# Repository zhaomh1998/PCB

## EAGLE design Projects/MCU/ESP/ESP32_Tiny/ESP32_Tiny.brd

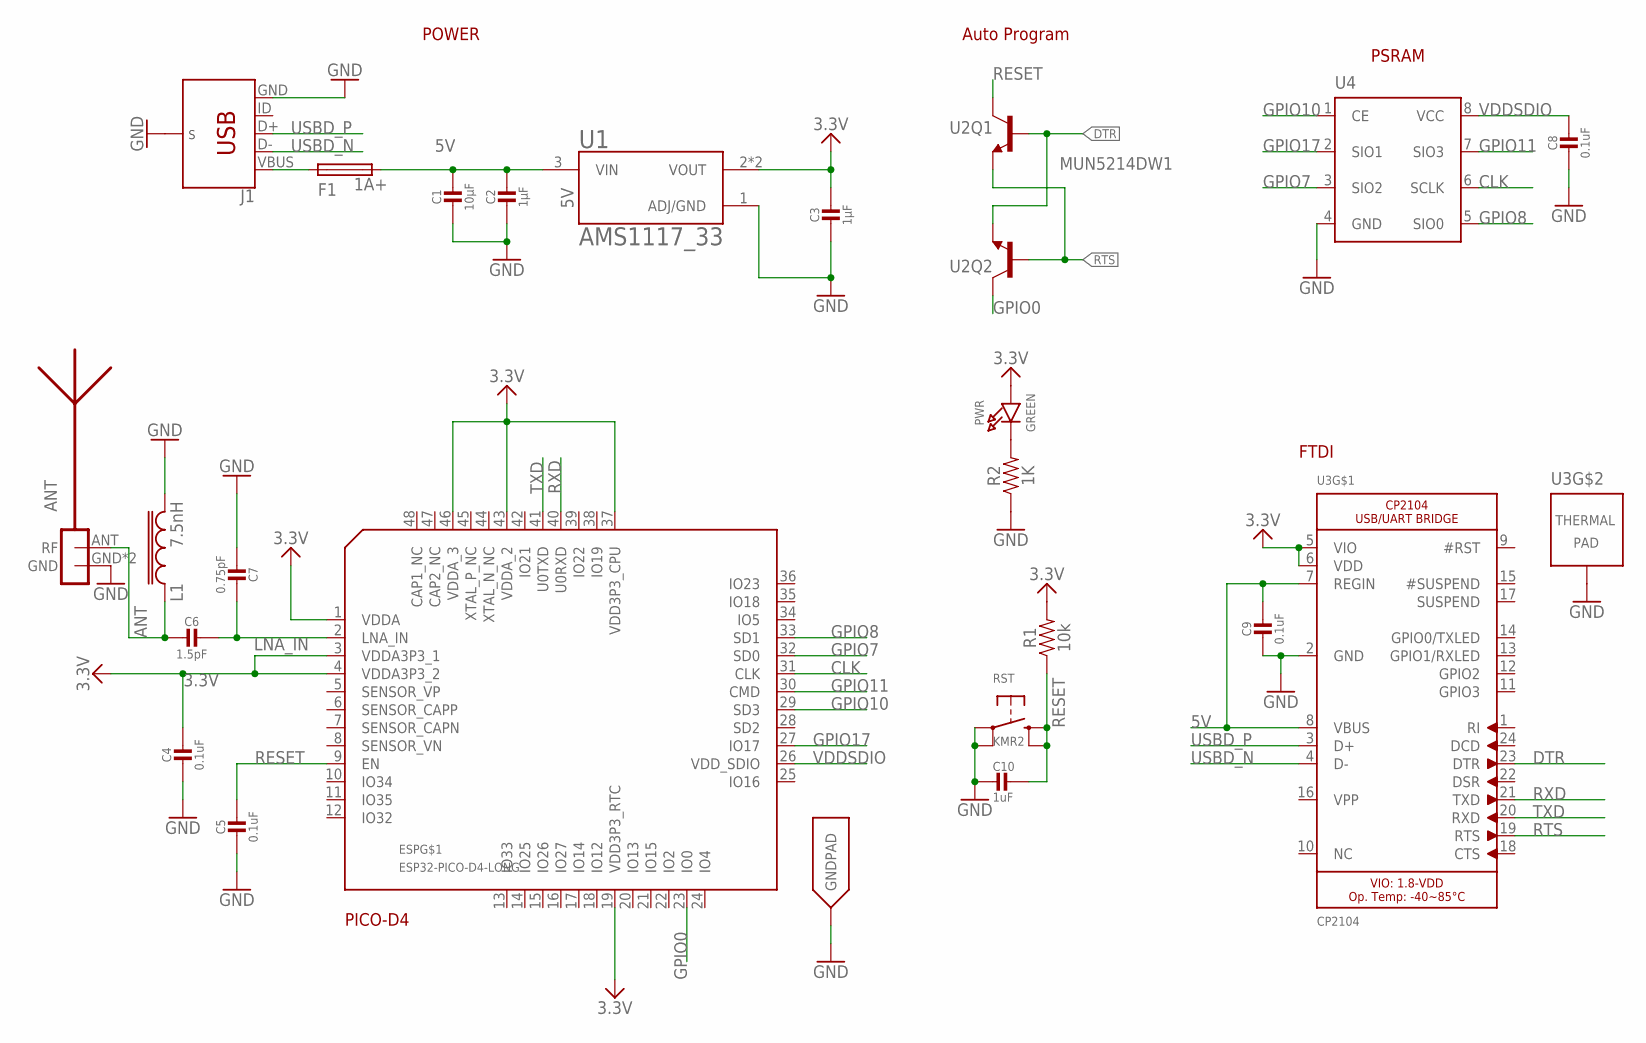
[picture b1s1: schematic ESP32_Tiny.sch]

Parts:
ANT: AN043_2.45GREV1_RIGHT; AN043_RIGHT
C1: 10µF; 0805
C2, C3: 1µF; 0603
C4, C5, C8, C9: 0.1uF; 0603
C6: 1.5pF; 0603
C7: 0.75pF; 0603
C10: 1uF; 0603
ESP: ESP32-PICO-D4-LONG; PICO-D4-QFN48-LONG
F1: 1A+; 1206
J1: USB-MICRO-B-SOCKET-2
L1: 7.5nH; 0603
PWR: GREEN; CHIPLED_0603
R1: 10k; 0603
R2: 1K; 0603
RST: KMR2; BTN_KMR2_4.6X2.8
U1: AMS1117_33; SOT89
U2: MUN5214DW1; DUAL_NPN_SC70-6
U3: CP2104; QFN24_4MM_SMSC_LONG
U4: LY68L6400SLIT; SOP8

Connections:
3.3V: C3.1, C4.1, ESP.1 (VDDA), ESP.3 (VDDA3P3_1), ESP.4 (VDDA3P3_2), ESP.19 (VDD3P3_RTC), ESP.37 (VDD3P3_CPU), ESP.43 (VDDA_2), ESP.46 (VDDA_3), PWR.A, R1.2, U1.2 (VOUT), U1.2@1 (VOUT), U3.5 (VIO), U3.6 (VDD)
5V: C1.1, C2.1, C9.1, F1.2, U1.3 (VIN), U3.7 (REGIN), U3.8 (VBUS)
ANT: ANT.ANT (RF), C6.2, L1.1
CLK: ESP.31 (CLK), U4.6 (SCLK)
DTR: U2.1 (E), U2.5 (B), U3.23 (DTR)
GND: ANT.GND, ANT.GND-PAD1 (GND), C1.2, C2.2, C3.2, C4.2, C5.2, C7.2, C8.2, C9.2, C10.2, ESP.EXP (GNDPAD), J1.GND, J1.S1 (SHIELD), J1.S2 (SHIELD), J1.S3 (SHIELD), J1.S4 (SHIELD), J1.S5 (SHIELD), L1.2, R2.1, RST.A, RST.A' (P1), U1.1 (ADJ/GND), U3.2 (GND), U3.THERM (TP), U4.4 (GND)
GPIO0: ESP.23 (IO0), U2.6 (C)
GPIO7: ESP.32 (SD0), U4.3 (SIO2)
GPIO8: ESP.33 (SD1), U4.5 (SIO0)
GPIO10: ESP.29 (SD3), U4.1 (CE)
GPIO11: ESP.30 (CMD), U4.7 (SIO3)
GPIO17: ESP.27 (IO17), U4.2 (SIO1)
LNA_IN: C6.1, C7.1, ESP.2 (LNA_IN)
unnamed: F1.1, J1.VBUS
unnamed: PWR.C, R2.2
RESET: C5.1, C10.1, ESP.9 (EN), R1.1, RST.B (S), RST.B' (S1), U2.3 (C)
RTS: U2.2 (B), U2.4 (E), U3.19 (RTS)
RXD: ESP.40 (U0RXD), U3.21 (TXD)
TXD: ESP.41 (U0TXD), U3.20 (RXD)
USBD_N: J1.D-, U3.4 (D-)
USBD_P: J1.D+, U3.3 (D+)
VDDSDIO: C8.1, ESP.26 (VDD_SDIO), U4.8 (VCC)

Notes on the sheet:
POWER
FTDI
PICO-D4
PSRAM
Auto Program

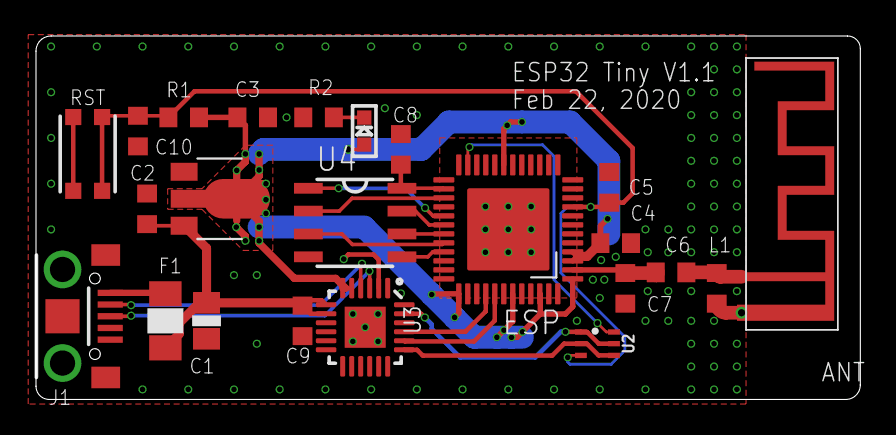
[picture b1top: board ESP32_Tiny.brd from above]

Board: 2 copper layers, 45.8 x 20.2 mm, 23 parts (0 on the bottom side), 22 nets.

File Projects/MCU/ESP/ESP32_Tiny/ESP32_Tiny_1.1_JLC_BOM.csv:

Comment,Designator,Footprint,LCSC Part #
10uF (106) ±10% 25V X5R,C1,805,C15850
1uF 0603,"C2,C3",603,C15849
0.1uF 0603,"C4,C5,C8,C9",603, C14663
1.5pF 0603,C6,603,C1639
0.75pF 0603,C7,603,C170124
ESP32-Pico-D4,ESP,,C193707
7.5nH 0603,L1,603,C395093
LED 0603,PWR,603,C72043
1K 0603,R1,603,C21190
10K 0603,R2,603,C25804
KMR211GLFS SWITCH TACTILE SPST-NO 0.05A 32V,RST,,
AMS1117,U1,SOT89,C108493
MUN5214DW1T1G TRANS 2NPN PREBIAS 0.25W SOT363,U2,SOT363,C94403
CP2104 IC SGL USB-TO-UART BRIDGE 24QFN,U3,24QFN,C47742
LY68L6400SLT Volatile 64Mb (8M x 8) SPI/ QPI 2.7V ~ 3.6V SOP-8_150mil RAM RoHS,U4,SOP8,C261881

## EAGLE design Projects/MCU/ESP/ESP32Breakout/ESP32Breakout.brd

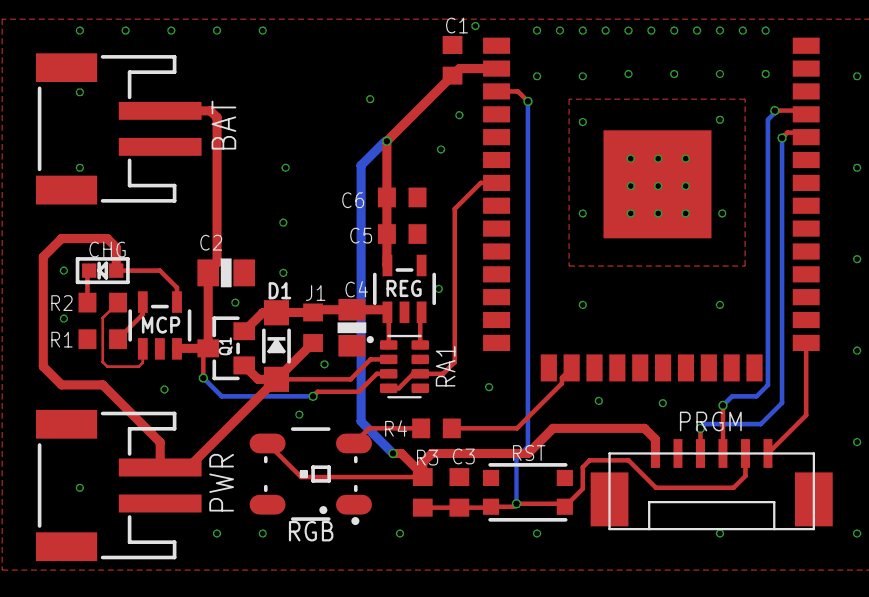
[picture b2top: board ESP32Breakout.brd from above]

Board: 2 copper layers, 23 parts (0 on the bottom side), 16 nets.

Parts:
BAT: JSTPH; JST_PH_2.0_2P
C1: 0.1uF; 0603
C2, C4: 10µF; 0805
C3, C5: 1uF; 0603
C6: 10µF; 0603
CHG: CHIPLED_0603
D1: MBR120; SOD-123
J1: 0603
MCP: MCP73831; MICROBUILDER_SOT23-5
PRGM: JST_1.25_6P; JST1.25_6P
PWR: JST_PH_2.0_2P
Q1: DMG3415U; SOT23-WIDE
R1: 4.7k; 0603
R2: 1k; 0603
R3: 10k; 0603
R4: 0603
RA1: RESCAF80P320X160X60-8N
REG: AP2112-3.3; MICROBUILDER_SOT23-5
RGB: LED_WS2812; LED-TRICOLOR-5050-IC
RST: KMR2; BTN_KMR2_4.6X2.8
X2: ESP32_WROOM32; WROOM32

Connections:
3.3V: C1.1, C5.1, C6.1, PRGM.6, R3.2, REG.5, RGB.VDD, X2.2
A13_I35: RA1.4, RA1.6, X2.7
EN: RA1.8, REG.3
GND: BAT.1, C1.2, C2.2, C3.2, C4.2, C5.2, C6.2, MCP.2, PRGM.5, PWR.1, R1.2, RA1.5, RA1.7, REG.2, RGB.VSS, RST.A, RST.A', X2.1, X2.15, X2.38, X2.P$1
GPIO0: PRGM.1, X2.25
IO13_A12: R4.2, X2.16
unnamed: CHG.C, R2.1
unnamed: R4.1, RGB.DIN
unnamed: MCP.1, R2.2
unnamed: MCP.5, R1.1
unnamed: C4.1, D1.C, J1.2, Q1.2, RA1.1, REG.1
RESET: C3.1, PRGM.2, R3.1, RST.B, RST.B', X2.3
RXD0: PRGM.4, X2.34
TXD0: PRGM.3, X2.35
VBAT: BAT.2, C2.1, MCP.3, Q1.3, RA1.3
VBUS: CHG.A, D1.A, J1.1, MCP.4, PWR.2, Q1.1, RA1.2

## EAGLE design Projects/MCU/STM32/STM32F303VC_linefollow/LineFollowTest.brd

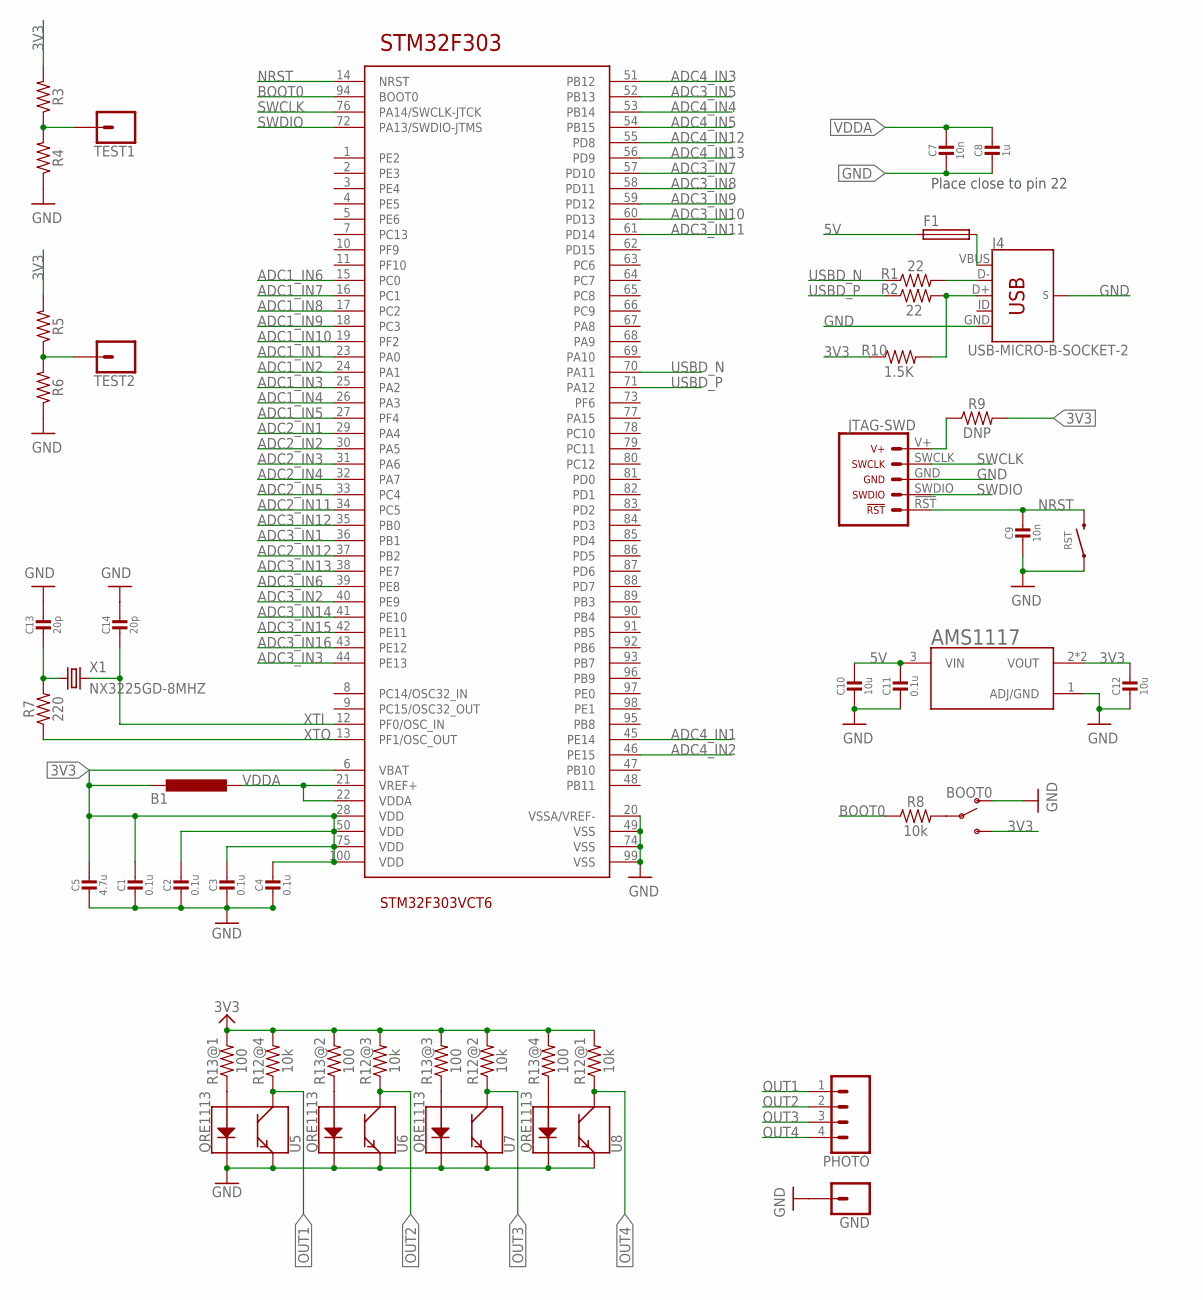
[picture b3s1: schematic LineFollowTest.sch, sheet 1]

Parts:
AMS1117: 3.3V; SOT89
B1: BEAD-0603; 0603
BOOT0: SWITCH_SPDT_SLIDE; SWITCH_SPDT_PTH_11.6X4.0MM
C1, C2, C3, C4, C11: 0.1u; CAP_0603
C5: 4.7u; CAP_0603
C7, C9: 10n; CAP_0603
C8: 1u; CAP_0603
C10, C12: 10u; CAP_0603
C13, C14: 20p; CAP_0603
F1: FUSE-1206; 1206
GND: THD_01; 1X01
J4: USB-MICRO-B-SOCKET-2
PHOTO: CONN_04PTH; 1X04
R1, R2: 22; 0603
R3, R4, R5, R6: 0603
R7: 220; 0603
R8: 10k; 0603
R9: DNP; 0603
R10: 1.5K; 0603
R12: 10k; RESCAF80P320X160X60-8N
R13: 100; RESCAF80P320X160X60-8N
RST: PUSHBUTTON; TACTILE_SWITCH_SMD_6.0X3.5MM
STM32F303: STM32F303VCT6; LQFP-100
TEST1, TEST2: THD_01; 1X01
U5, U6, U7, U8: QRE1113; QRE1113-W
U$3: JTAG-SWD; JTAG_SWD
X1: NX3225GD-8MHZ; XTAL-SMD-3225

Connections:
3V3: AMS1117.2 (VOUT), AMS1117.2@1 (VOUT), B1.1, BOOT0.3 (S), C1.1, C2.1, C3.1, C4.1, C5.1, C12.1, R3.2, R5.2, R9.2, R10.1, R12.5 (2), R12.6 (2), R12.7 (2), R12.8 (2), R13.5 (2), R13.6 (2), R13.7 (2), R13.8 (2), STM32F303.6 (VBAT), STM32F303.28 (VDD), STM32F303.50 (VDD), STM32F303.75 (VDD), STM32F303.100 (VDD)
5V: AMS1117.3 (VIN), C10.1, C11.1, F1.1
ADC1_IN1: STM32F303.23 (PA0); also elsewhere on the board
ADC1_IN2: STM32F303.24 (PA1); also elsewhere on the board
ADC1_IN3: STM32F303.25 (PA2); also elsewhere on the board
ADC1_IN4: STM32F303.26 (PA3); also elsewhere on the board
ADC1_IN5: STM32F303.27 (PF4); also elsewhere on the board
ADC1_IN6: STM32F303.15 (PC0); also elsewhere on the board
ADC1_IN7: STM32F303.16 (PC1); also elsewhere on the board
ADC1_IN8: STM32F303.17 (PC2); also elsewhere on the board
ADC1_IN9: STM32F303.18 (PC3); also elsewhere on the board
ADC1_IN10: STM32F303.19 (PF2); also elsewhere on the board
ADC2_IN1: STM32F303.29 (PA4); also elsewhere on the board
ADC2_IN2: STM32F303.30 (PA5); also elsewhere on the board
ADC2_IN3: STM32F303.31 (PA6); also elsewhere on the board
ADC2_IN4: STM32F303.32 (PA7); also elsewhere on the board
ADC2_IN5: STM32F303.33 (PC4); also elsewhere on the board
ADC2_IN11: STM32F303.34 (PC5); also elsewhere on the board
ADC2_IN12: STM32F303.37 (PB2); also elsewhere on the board
ADC3_IN1: STM32F303.36 (PB1); also elsewhere on the board
ADC3_IN2: STM32F303.40 (PE9); also elsewhere on the board
ADC3_IN3: STM32F303.44 (PE13); also elsewhere on the board
ADC3_IN5: STM32F303.52 (PB13); also elsewhere on the board
ADC3_IN6: STM32F303.39 (PE8); also elsewhere on the board
ADC3_IN7: STM32F303.57 (PD10); also elsewhere on the board
ADC3_IN8: STM32F303.58 (PD11); also elsewhere on the board
ADC3_IN9: STM32F303.59 (PD12); also elsewhere on the board
ADC3_IN10: STM32F303.60 (PD13); also elsewhere on the board
ADC3_IN11: STM32F303.61 (PD14); also elsewhere on the board
ADC3_IN12: STM32F303.35 (PB0); also elsewhere on the board
ADC3_IN13: STM32F303.38 (PE7); also elsewhere on the board
ADC3_IN14: STM32F303.41 (PE10); also elsewhere on the board
ADC3_IN15: STM32F303.42 (PE11); also elsewhere on the board
ADC3_IN16: STM32F303.43 (PE12); also elsewhere on the board
ADC4_IN1: STM32F303.45 (PE14); also elsewhere on the board
ADC4_IN2: STM32F303.46 (PE15); also elsewhere on the board
ADC4_IN3: STM32F303.51 (PB12); also elsewhere on the board
ADC4_IN4: STM32F303.53 (PB14); also elsewhere on the board
ADC4_IN5: STM32F303.54 (PB15); also elsewhere on the board
ADC4_IN12: STM32F303.55 (PD8); also elsewhere on the board
ADC4_IN13: STM32F303.56 (PD9); also elsewhere on the board
BOOT0: R8.1, STM32F303.94 (BOOT0)
GND: AMS1117.1 (ADJ/GND), BOOT0.1 (O), C1.2, C2.2, C3.2, C4.2, C5.2, C7.2, C8.2, C9.2, C10.2, C11.2, C12.2, C13.1, C14.1, GND.1, J4.GND, J4.S1 (SHIELD), J4.S2 (SHIELD), J4.S3 (SHIELD), J4.S4 (SHIELD), J4.S5 (SHIELD), R4.1, R6.1, RST.1, STM32F303.20 (VSSA/VREF-), STM32F303.49 (VSS), STM32F303.74 (VSS), STM32F303.99 (VSS), U5.2 (K), U5.4 (E), U6.2 (K), U6.4 (E), U7.2 (K), U7.4 (E), U8.2 (K), U8.4 (E), U$3.GND
unnamed: R5.1, R6.2, TEST2.1
unnamed: C13.2, R7.2, X1.1
unnamed: BOOT0.2, R8.2
unnamed: R9.1, U$3.V+
unnamed: R3.1, R4.2, TEST1.1
unnamed: F1.2, J4.VBUS
unnamed: J4.D-, R1.2
unnamed: J4.D+, R2.2, R10.2
unnamed: R13.1, U5.1 (A)
unnamed: R13.2 (1), U6.1 (A)
unnamed: R13.3 (1), U7.1 (A)
unnamed: R13.4 (1), U8.1 (A)
NRST: C9.1, RST.2, STM32F303.14 (NRST), U$3.!RST
OUT1: PHOTO.1, R12.4 (1), U5.3 (C)
OUT2: PHOTO.2, R12.3 (1), U6.3 (C)
OUT3: PHOTO.3, R12.2 (1), U7.3 (C)
OUT4: PHOTO.4, R12.1, U8.3 (C)
SWCLK: STM32F303.76 (PA14/SWCLK-JTCK), U$3.SWCLK
SWDIO: STM32F303.72 (PA13/SWDIO-JTMS), U$3.SWDIO
USBD_N: R1.1, STM32F303.70 (PA11)
USBD_P: R2.1, STM32F303.71 (PA12)
VDDA: B1.2, C7.1, C8.1, STM32F303.21 (VREF+), STM32F303.22 (VDDA)
XTI: C14.2, STM32F303.12 (PF0/OSC_IN), X1.2
XTO: R7.1, STM32F303.13 (PF1/OSC_OUT)

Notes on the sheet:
Place close to pin 22

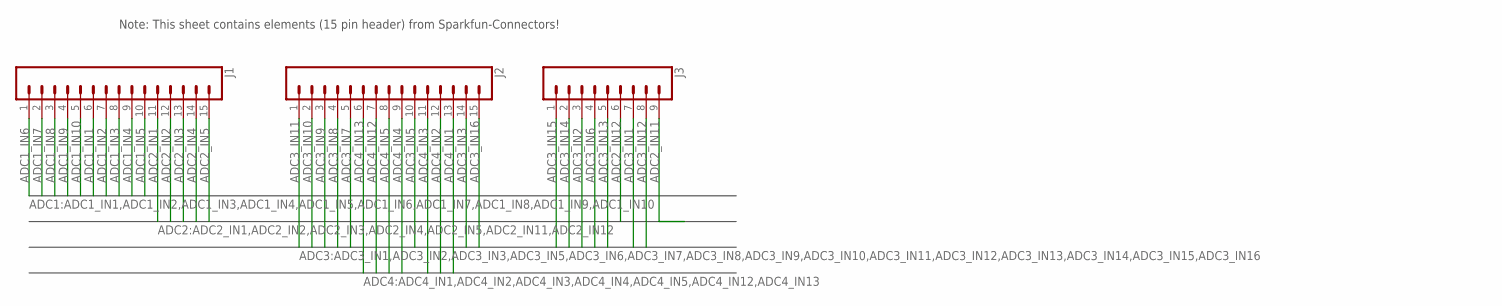
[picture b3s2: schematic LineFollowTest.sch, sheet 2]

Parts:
J1, J2: CONN_15; 1X15
J3: CONN_09; 1X09

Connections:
ADC1_IN1: J1.6; also elsewhere on the board
ADC1_IN2: J1.7; also elsewhere on the board
ADC1_IN3: J1.8; also elsewhere on the board
ADC1_IN4: J1.9; also elsewhere on the board
ADC1_IN5: J1.10; also elsewhere on the board
ADC1_IN6: J1.1; also elsewhere on the board
ADC1_IN7: J1.2; also elsewhere on the board
ADC1_IN8: J1.3; also elsewhere on the board
ADC1_IN9: J1.4; also elsewhere on the board
ADC1_IN10: J1.5; also elsewhere on the board
ADC2_IN1: J1.11; also elsewhere on the board
ADC2_IN2: J1.12; also elsewhere on the board
ADC2_IN3: J1.13; also elsewhere on the board
ADC2_IN4: J1.14; also elsewhere on the board
ADC2_IN5: J1.15; also elsewhere on the board
ADC2_IN11: J3.9; also elsewhere on the board
ADC2_IN12: J3.6; also elsewhere on the board
ADC3_IN1: J3.7; also elsewhere on the board
ADC3_IN2: J3.3; also elsewhere on the board
ADC3_IN3: J2.14; also elsewhere on the board
ADC3_IN5: J2.10; also elsewhere on the board
ADC3_IN6: J3.4; also elsewhere on the board
ADC3_IN7: J2.5; also elsewhere on the board
ADC3_IN8: J2.4; also elsewhere on the board
ADC3_IN9: J2.3; also elsewhere on the board
ADC3_IN10: J2.2; also elsewhere on the board
ADC3_IN11: J2.1; also elsewhere on the board
ADC3_IN12: J3.8; also elsewhere on the board
ADC3_IN13: J3.5; also elsewhere on the board
ADC3_IN14: J3.2; also elsewhere on the board
ADC3_IN15: J3.1; also elsewhere on the board
ADC3_IN16: J2.15; also elsewhere on the board
ADC4_IN1: J2.13; also elsewhere on the board
ADC4_IN2: J2.12; also elsewhere on the board
ADC4_IN3: J2.11; also elsewhere on the board
ADC4_IN4: J2.9; also elsewhere on the board
ADC4_IN5: J2.8; also elsewhere on the board
ADC4_IN12: J2.7; also elsewhere on the board
ADC4_IN13: J2.6; also elsewhere on the board

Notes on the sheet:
Note: This sheet contains elements (15 pin header) from Sparkfun-Connectors!

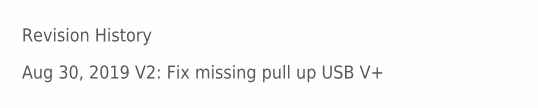
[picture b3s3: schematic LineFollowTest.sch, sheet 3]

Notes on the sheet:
Revision History
Aug 30, 2019 V2: Fix missing pull up USB V+

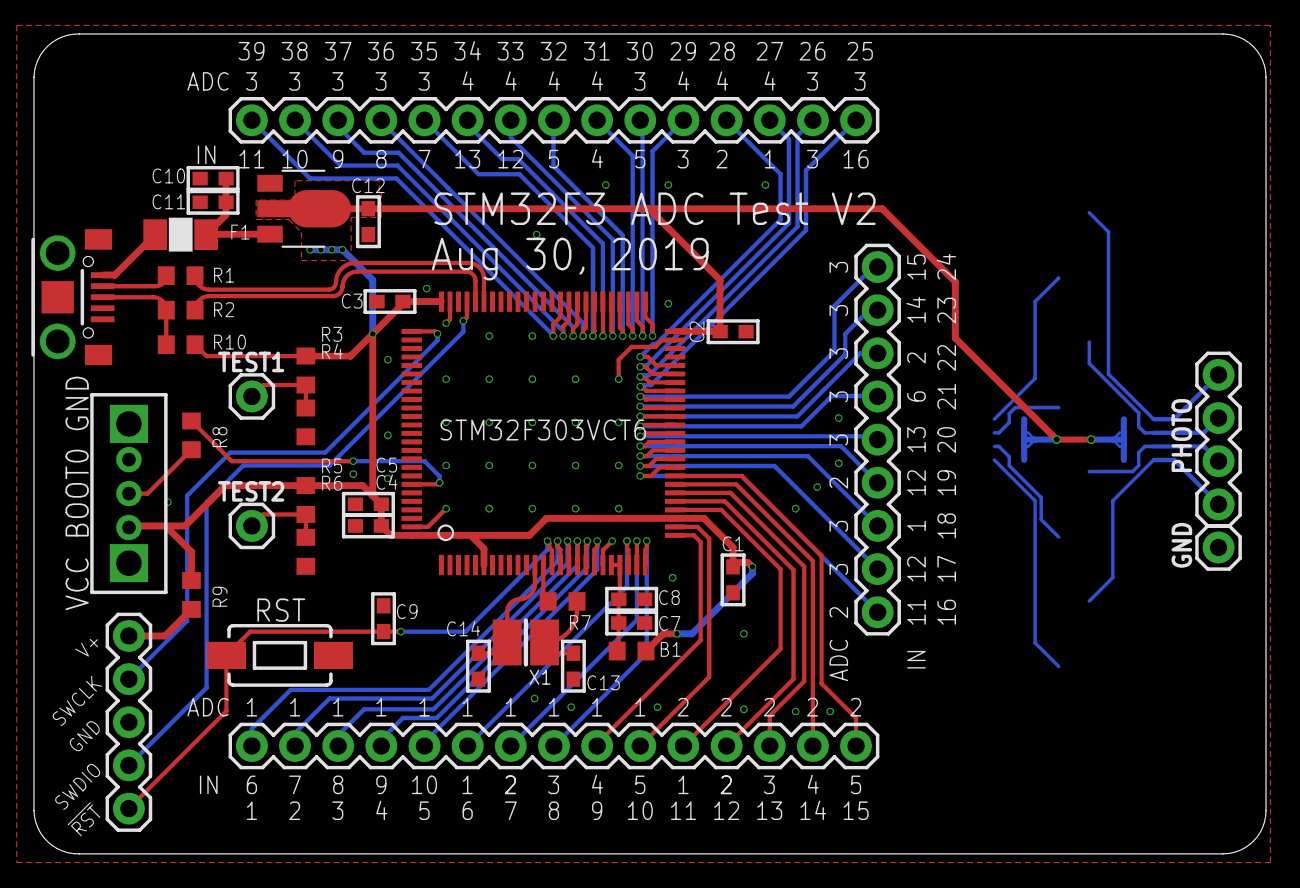
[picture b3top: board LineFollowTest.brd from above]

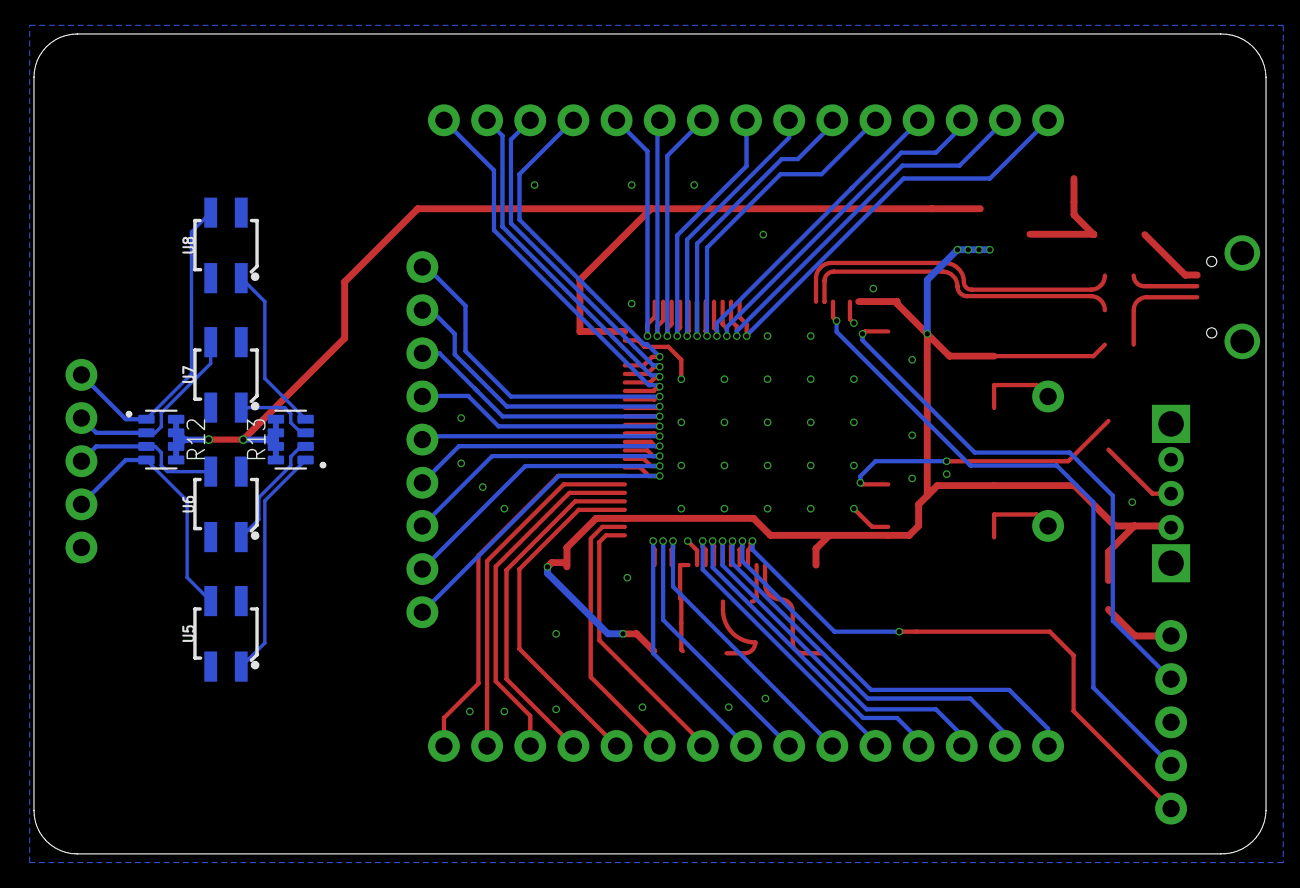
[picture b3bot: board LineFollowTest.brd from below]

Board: 2 copper layers, 72.5 x 48.3 mm, 45 parts (6 on the bottom side), 67 nets.

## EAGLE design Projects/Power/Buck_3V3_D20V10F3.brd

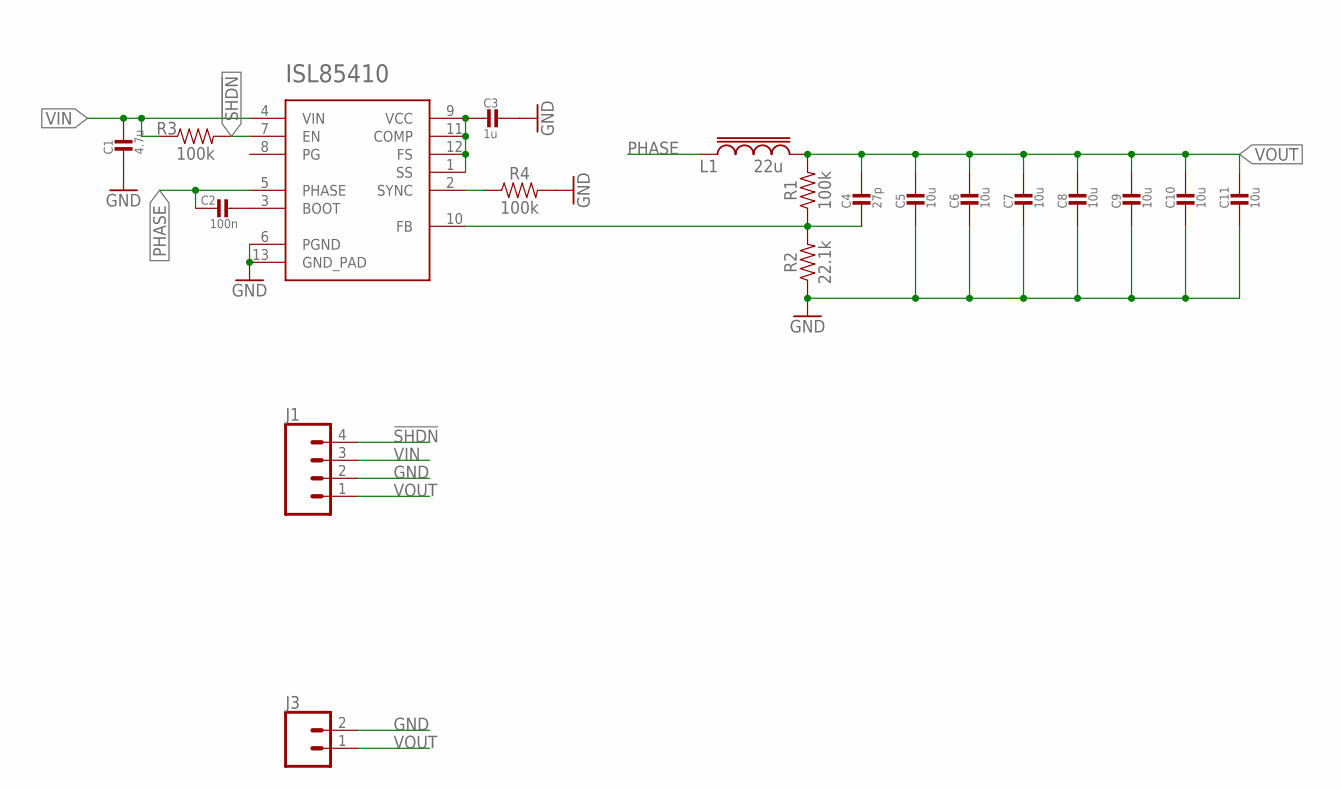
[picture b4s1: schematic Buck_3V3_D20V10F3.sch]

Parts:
C1: 4.7u; 0603
C2: 100n; 0603
C3: 1u; 0603
C4: 27p; 0603
C5, C6, C7, C8, C9, C10, C11: 10u; 0805
ISL85410: BUCK_ISL85410; DFN-12_DE-L
J1: CONN_041X04_NO_SILK; 1X04_NO_SILK
J3: CONN_021X02_NO_SILK; 1X02_NO_SILK
L1: 22u; CD54
R1, R3, R4: 100k; 0603
R2: 22.1k; 0603

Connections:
!SHDN: ISL85410.7 (EN), J1.4, R3.2
BOOT: C2.1, ISL85410.3 (BOOT)
FB: C4.2, ISL85410.10 (FB), R1.1, R2.2
GND: C1.2, C3.1, C5.2, C6.2, C7.2, C8.2, C9.2, C10.2, C11.2, ISL85410.6 (PGND), ISL85410.13 (GND_PAD), J1.2, J3.2, R2.1, R4.2
PHASE: C2.2, ISL85410.5 (PHASE), L1.P$1
SYNC: ISL85410.2 (SYNC), R4.1
VCC: C3.2, ISL85410.1 (SS), ISL85410.9 (VCC), ISL85410.11 (COMP), ISL85410.12 (FS)
VIN: C1.1, ISL85410.4 (VIN), J1.3, R3.1
VOUT: C4.1, C5.1, C6.1, C7.1, C8.1, C9.1, C10.1, C11.1, J1.1, J3.1, L1.P$2, R1.2

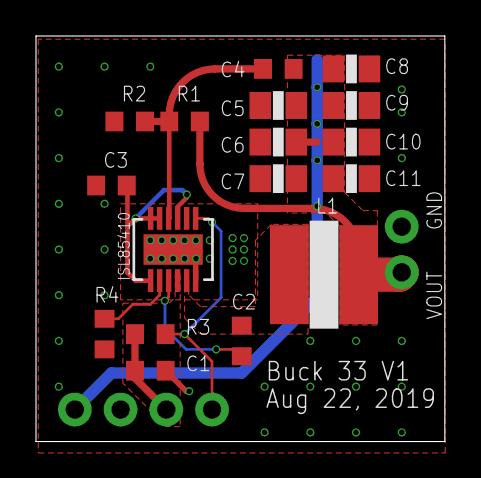
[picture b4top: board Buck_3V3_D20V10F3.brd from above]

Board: 2 copper layers, 22.7 x 22.5 mm, 19 parts (0 on the bottom side), 9 nets.

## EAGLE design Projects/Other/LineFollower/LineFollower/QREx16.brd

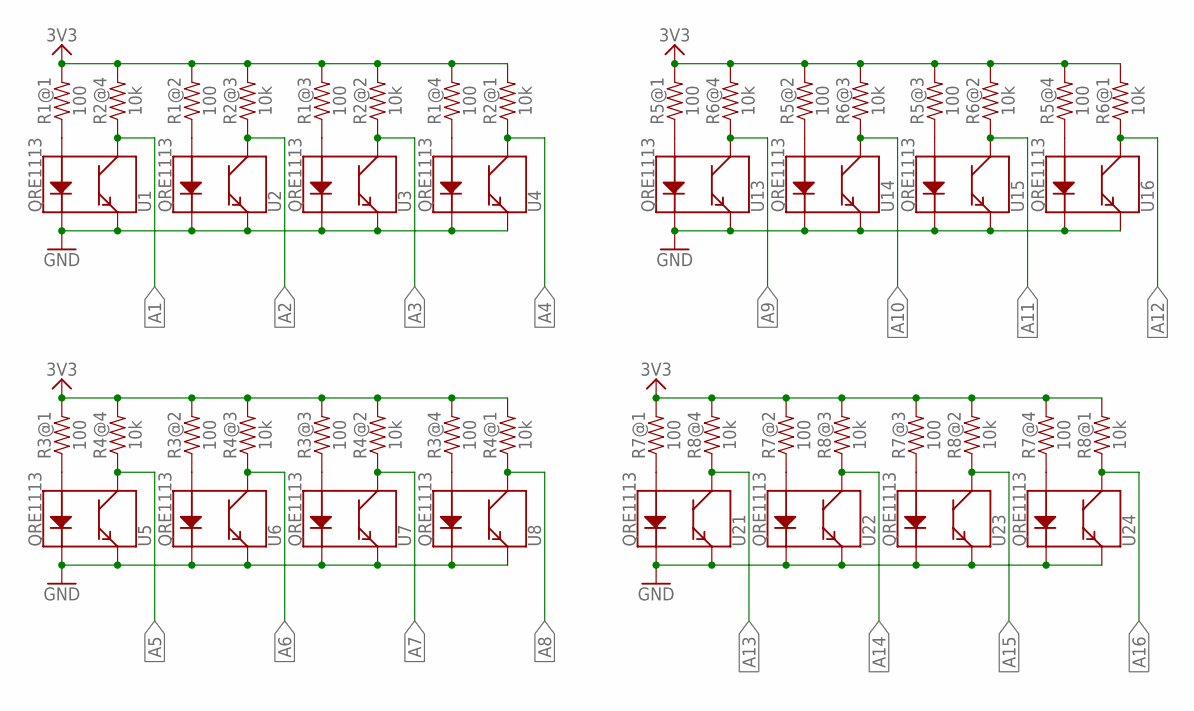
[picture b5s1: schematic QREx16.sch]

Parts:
R1, R3, R5, R7: 100; RESCAF80P320X160X60-8N
R2, R4, R6, R8: 10k; RESCAF80P320X160X60-8N
U1, U2, U3, U4, U5, U6, U7, U8, U13, U14, U15, U16, U21, U22, U23, U24: QRE1113; QRE1113-W

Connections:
3.3V: R1.5 (2), R1.6 (2), R1.7 (2), R1.8 (2), R2.5 (2), R2.6 (2), R2.7 (2), R2.8 (2), R3.5 (2), R3.6 (2), R3.7 (2), R3.8 (2), R4.5 (2), R4.6 (2), R4.7 (2), R4.8 (2), R5.5 (2), R5.6 (2), R5.7 (2), R5.8 (2), R6.5 (2), R6.6 (2), R6.7 (2), R6.8 (2), R7.5 (2), R7.6 (2), R7.7 (2), R7.8 (2), R8.5 (2), R8.6 (2), R8.7 (2), R8.8 (2)
A1: R2.4 (1), U1.3 (C)
A2: R2.3 (1), U2.3 (C)
A3: R2.2 (1), U3.3 (C)
A4: R2.1, U4.3 (C)
A5: R4.4 (1), U5.3 (C)
A6: R4.3 (1), U6.3 (C)
A7: R4.2 (1), U7.3 (C)
A8: R4.1, U8.3 (C)
A9: R6.4 (1), U13.3 (C)
A10: R6.3 (1), U14.3 (C)
A11: R6.2 (1), U15.3 (C)
A12: R6.1, U16.3 (C)
A13: R8.4 (1), U21.3 (C)
A14: R8.3 (1), U22.3 (C)
A15: R8.2 (1), U23.3 (C)
A16: R8.1, U24.3 (C)
GND: U1.2 (K), U1.4 (E), U2.2 (K), U2.4 (E), U3.2 (K), U3.4 (E), U4.2 (K), U4.4 (E), U5.2 (K), U5.4 (E), U6.2 (K), U6.4 (E), U7.2 (K), U7.4 (E), U8.2 (K), U8.4 (E), U13.2 (K), U13.4 (E), U14.2 (K), U14.4 (E), U15.2 (K), U15.4 (E), U16.2 (K), U16.4 (E), U21.2 (K), U21.4 (E), U22.2 (K), U22.4 (E), U23.2 (K), U23.4 (E), U24.2 (K), U24.4 (E)
unnamed: R1.1, U1.1 (A)
unnamed: R1.2 (1), U2.1 (A)
unnamed: R1.3 (1), U3.1 (A)
unnamed: R1.4 (1), U4.1 (A)
unnamed: R3.1, U5.1 (A)
unnamed: R3.2 (1), U6.1 (A)
unnamed: R3.3 (1), U7.1 (A)
unnamed: R3.4 (1), U8.1 (A)
unnamed: R5.1, U13.1 (A)
unnamed: R5.2 (1), U14.1 (A)
unnamed: R5.3 (1), U15.1 (A)
unnamed: R5.4 (1), U16.1 (A)
unnamed: R7.1, U21.1 (A)
unnamed: R7.2 (1), U22.1 (A)
unnamed: R7.3 (1), U23.1 (A)
unnamed: R7.4 (1), U24.1 (A)

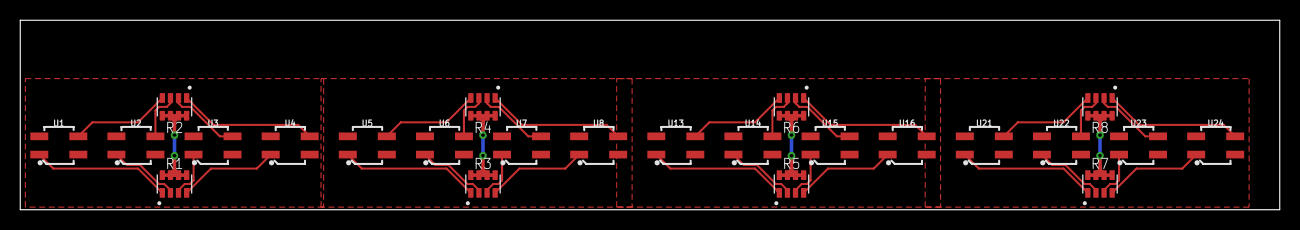
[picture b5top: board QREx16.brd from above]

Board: 2 copper layers, 124.4 x 18.7 mm, 24 parts (0 on the bottom side), 34 nets.

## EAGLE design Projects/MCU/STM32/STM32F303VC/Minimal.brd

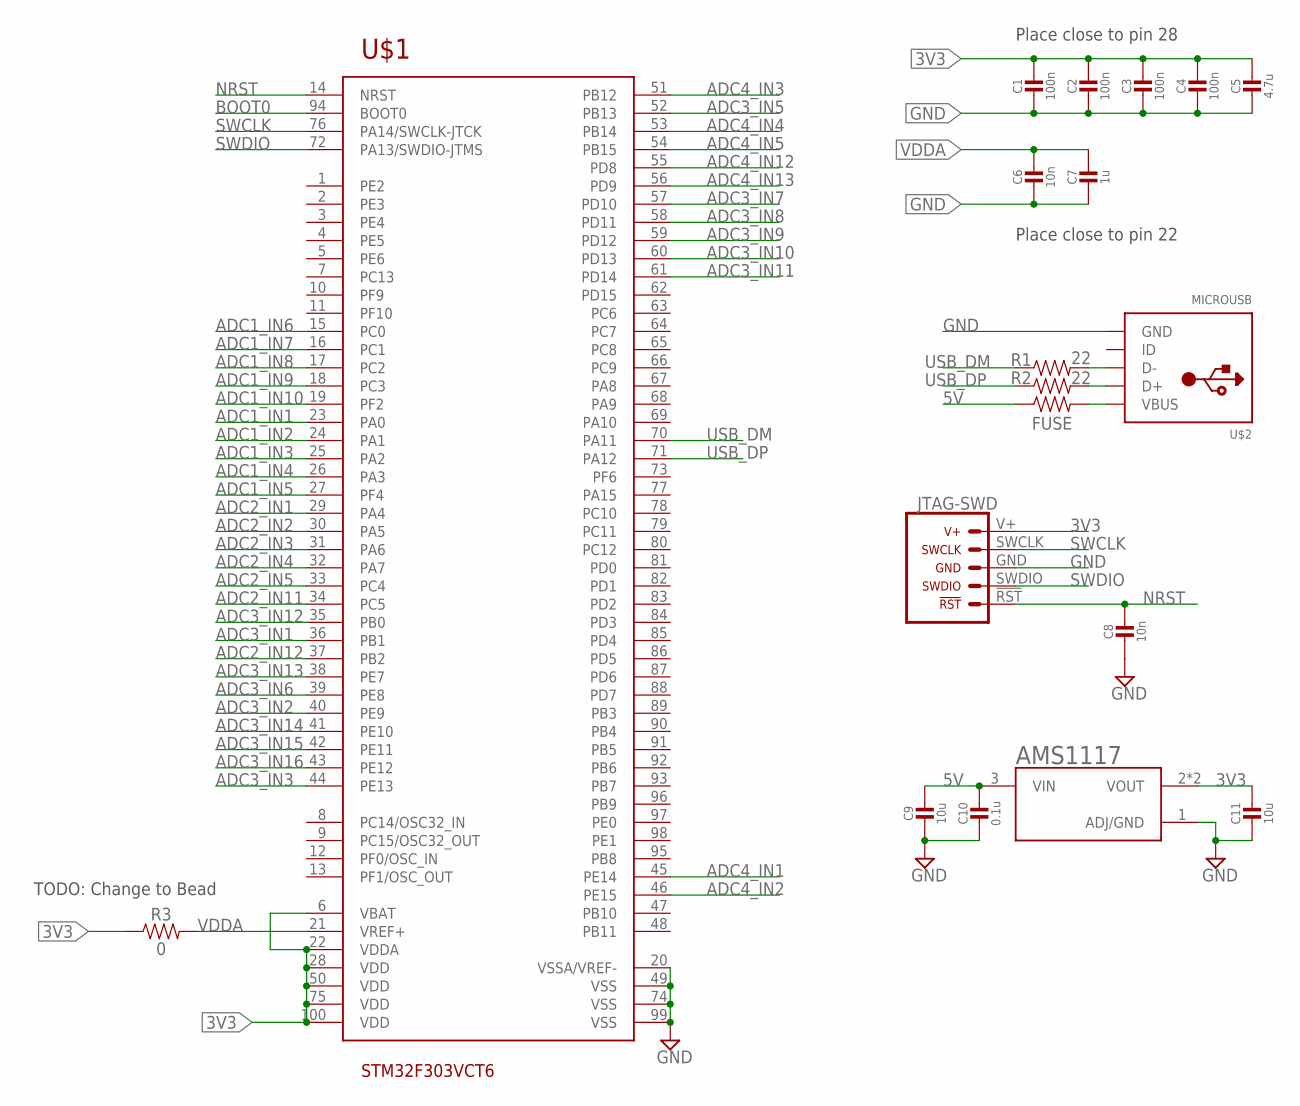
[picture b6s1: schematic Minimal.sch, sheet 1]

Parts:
AMS1117: 3.3V; SOT89
C1, C2, C3, C4: 100n; CAP_0603
C5: 4.7u; CAP_0603
C6, C8: 10n; CAP_0603
C7: 1u; CAP_0603
C9, C11: 10u; CAP_0603
C10: 0.1u; CAP_0603
FUSE: 1206
R1, R2: 22; 0603
R3: 0; 0603
U$1: STM32F303VCT6; LQFP-100
U$2: MICROUSB
U$3: JTAG-SWD; JTAG_SWD

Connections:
3V3: AMS1117.2 (VOUT), AMS1117.2@1 (VOUT), C1.1, C2.1, C3.1, C4.1, C5.1, C11.1, R3.1, U$1.6 (VBAT), U$1.22 (VDDA), U$1.28 (VDD), U$1.50 (VDD), U$1.75 (VDD), U$1.100 (VDD), U$3.V+
5V: AMS1117.3 (VIN), C9.1, C10.1, FUSE.1
ADC1_IN1: U$1.23 (PA0); also elsewhere on the board
ADC1_IN2: U$1.24 (PA1); also elsewhere on the board
ADC1_IN3: U$1.25 (PA2); also elsewhere on the board
ADC1_IN4: U$1.26 (PA3); also elsewhere on the board
ADC1_IN5: U$1.27 (PF4); also elsewhere on the board
ADC1_IN6: U$1.15 (PC0); also elsewhere on the board
ADC1_IN7: U$1.16 (PC1); also elsewhere on the board
ADC1_IN8: U$1.17 (PC2); also elsewhere on the board
ADC1_IN9: U$1.18 (PC3); also elsewhere on the board
ADC1_IN10: U$1.19 (PF2); also elsewhere on the board
ADC2_IN1: U$1.29 (PA4); also elsewhere on the board
ADC2_IN2: U$1.30 (PA5); also elsewhere on the board
ADC2_IN3: U$1.31 (PA6); also elsewhere on the board
ADC2_IN4: U$1.32 (PA7); also elsewhere on the board
ADC2_IN5: U$1.33 (PC4); also elsewhere on the board
ADC2_IN11: U$1.34 (PC5); also elsewhere on the board
ADC2_IN12: U$1.37 (PB2); also elsewhere on the board
ADC3_IN1: U$1.36 (PB1); also elsewhere on the board
ADC3_IN2: U$1.40 (PE9); also elsewhere on the board
ADC3_IN3: U$1.44 (PE13); also elsewhere on the board
ADC3_IN5: U$1.52 (PB13); also elsewhere on the board
ADC3_IN6: U$1.39 (PE8); also elsewhere on the board
ADC3_IN7: U$1.57 (PD10); also elsewhere on the board
ADC3_IN8: U$1.58 (PD11); also elsewhere on the board
ADC3_IN9: U$1.59 (PD12); also elsewhere on the board
ADC3_IN10: U$1.60 (PD13); also elsewhere on the board
ADC3_IN11: U$1.61 (PD14); also elsewhere on the board
ADC3_IN12: U$1.35 (PB0); also elsewhere on the board
ADC3_IN13: U$1.38 (PE7); also elsewhere on the board
ADC3_IN14: U$1.41 (PE10); also elsewhere on the board
ADC3_IN15: U$1.42 (PE11); also elsewhere on the board
ADC3_IN16: U$1.43 (PE12); also elsewhere on the board
ADC4_IN1: U$1.45 (PE14); also elsewhere on the board
ADC4_IN2: U$1.46 (PE15); also elsewhere on the board
ADC4_IN3: U$1.51 (PB12); also elsewhere on the board
ADC4_IN4: U$1.53 (PB14); also elsewhere on the board
ADC4_IN5: U$1.54 (PB15); also elsewhere on the board
ADC4_IN12: U$1.55 (PD8); also elsewhere on the board
ADC4_IN13: U$1.56 (PD9); also elsewhere on the board
BOOT0: U$1.94 (BOOT0)
GND: AMS1117.1 (ADJ/GND), C1.2, C2.2, C3.2, C4.2, C5.2, C6.2, C7.2, C8.2, C9.2, C10.2, C11.2, U$1.20 (VSSA/VREF-), U$1.49 (VSS), U$1.74 (VSS), U$1.99 (VSS), U$2.GND, U$2.S1 (GND), U$2.S2 (GND), U$2.S3 (GND), U$2.S4 (GND), U$2.S5 (GND), U$2.S6 (GND), U$3.GND
unnamed: FUSE.2, U$2.VBUS
unnamed: R2.2, U$2.D+
unnamed: R1.2, U$2.D-
NRST: C8.1, U$1.14 (NRST), U$3.!RST
SWCLK: U$1.76 (PA14/SWCLK-JTCK), U$3.SWCLK
SWDIO: U$1.72 (PA13/SWDIO-JTMS), U$3.SWDIO
USB_DM: R1.1, U$1.70 (PA11)
USB_DP: R2.1, U$1.71 (PA12)
VDDA: C6.1, C7.1, R3.2, U$1.21 (VREF+)

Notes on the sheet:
Place close to pin 28
Place close to pin 22
TODO: Change to Bead

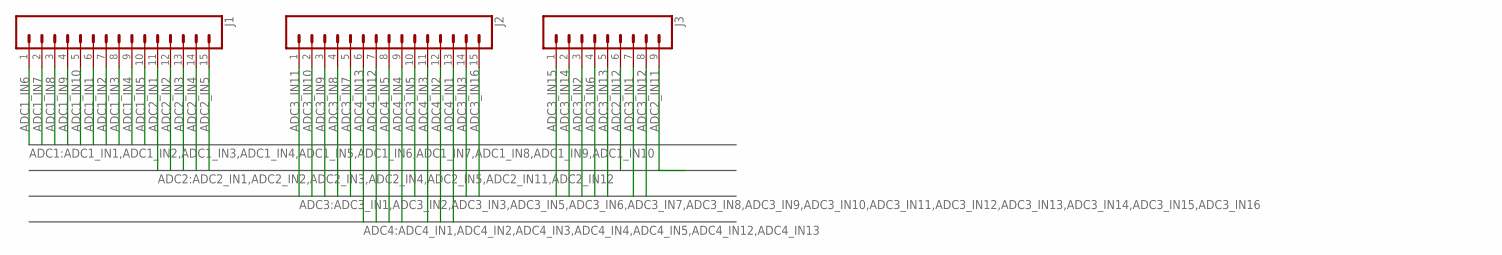
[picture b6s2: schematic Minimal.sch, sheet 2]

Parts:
J1, J2: CONN_15; 1X15
J3: CONN_09; 1X09

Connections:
ADC1_IN1: J1.6; also elsewhere on the board
ADC1_IN2: J1.7; also elsewhere on the board
ADC1_IN3: J1.8; also elsewhere on the board
ADC1_IN4: J1.9; also elsewhere on the board
ADC1_IN5: J1.10; also elsewhere on the board
ADC1_IN6: J1.1; also elsewhere on the board
ADC1_IN7: J1.2; also elsewhere on the board
ADC1_IN8: J1.3; also elsewhere on the board
ADC1_IN9: J1.4; also elsewhere on the board
ADC1_IN10: J1.5; also elsewhere on the board
ADC2_IN1: J1.11; also elsewhere on the board
ADC2_IN2: J1.12; also elsewhere on the board
ADC2_IN3: J1.13; also elsewhere on the board
ADC2_IN4: J1.14; also elsewhere on the board
ADC2_IN5: J1.15; also elsewhere on the board
ADC2_IN11: J3.9; also elsewhere on the board
ADC2_IN12: J3.6; also elsewhere on the board
ADC3_IN1: J3.7; also elsewhere on the board
ADC3_IN2: J3.3; also elsewhere on the board
ADC3_IN3: J2.14; also elsewhere on the board
ADC3_IN5: J2.10; also elsewhere on the board
ADC3_IN6: J3.4; also elsewhere on the board
ADC3_IN7: J2.5; also elsewhere on the board
ADC3_IN8: J2.4; also elsewhere on the board
ADC3_IN9: J2.3; also elsewhere on the board
ADC3_IN10: J2.2; also elsewhere on the board
ADC3_IN11: J2.1; also elsewhere on the board
ADC3_IN12: J3.8; also elsewhere on the board
ADC3_IN13: J3.5; also elsewhere on the board
ADC3_IN14: J3.2; also elsewhere on the board
ADC3_IN15: J3.1; also elsewhere on the board
ADC3_IN16: J2.15; also elsewhere on the board
ADC4_IN1: J2.13; also elsewhere on the board
ADC4_IN2: J2.12; also elsewhere on the board
ADC4_IN3: J2.11; also elsewhere on the board
ADC4_IN4: J2.9; also elsewhere on the board
ADC4_IN5: J2.8; also elsewhere on the board
ADC4_IN12: J2.7; also elsewhere on the board
ADC4_IN13: J2.6; also elsewhere on the board

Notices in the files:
parts and their libraries:
SparkFun-Connectors: Licensing: Creative Commons ShareAlike 4.0 International - https://creativecommons.org/licenses/by-sa/4.0
